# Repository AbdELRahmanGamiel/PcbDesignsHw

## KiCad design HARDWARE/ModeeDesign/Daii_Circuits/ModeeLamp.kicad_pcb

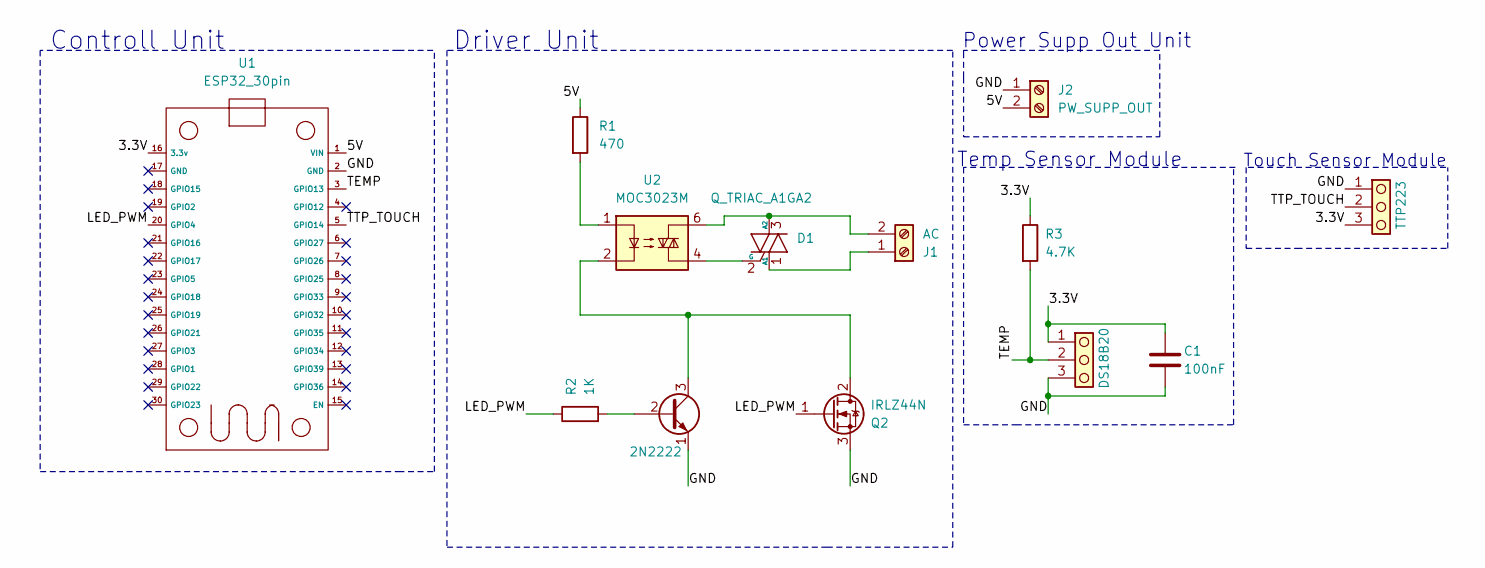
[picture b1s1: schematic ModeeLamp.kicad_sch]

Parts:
C1: 100nF; C_Disc_D5.0mm_W2.5mm_P2.50mm
D1: Q_TRIAC_A1GA2; TO-220-3_Vertical
J1: AC; Altech_AK100_1x02_P5.00mm
J2: PW_SUPP_OUT; Altech_AK100_1x02_P5.00mm
J3: DS18B20; Altech_AK100_1x03_P5.00mm
J4: TTP223; Altech_AK100_1x03_P5.00mm
Q1: 2N2222; TO-92L
Q2: IRLZ44N; TO-220-3_Vertical
R1: 470; R_Axial_DIN0204_L3.6mm_D1.6mm_P7.62mm_Horizontal
R2: 1K; R_Axial_DIN0204_L3.6mm_D1.6mm_P7.62mm_Horizontal
R3: 4.7K; R_Axial_DIN0204_L3.6mm_D1.6mm_P7.62mm_Horizontal
U1: ESP32_30pin
U2: MOC3023M; DIP-6_W7.62mm

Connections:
/3.3V: C1.1, J3.1, J4.3, R3.1, U1.16 (3.3v)
/5V: J2.2, R1.1, U1.1 (VIN)
/GND: C1.2, J2.1, J3.3, J4.1, Q1.1 (E), Q2.3 (S), U1.2 (GND)
/LED_PWM: Q2.1 (G), R2.1, U1.20 (GPIO4)
/TEMP: J3.2, R3.2, U1.3 (GPIO13)
/TTP_TOUCH: J4.2, U1.5 (GPIO14)
unnamed: D1.1 (A1), J1.1
unnamed: D1.3 (A2), J1.2, U2.6
unnamed: D1.2 (G), U2.4
unnamed: Q1.2 (B), R2.2
unnamed: Q1.3 (C), Q2.2 (D), U2.2
unnamed: R1.2, U2.1

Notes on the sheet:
Controll Unit
Temp Sensor Module
Power Supp Out Unit
Touch Sensor Module
Driver Unit

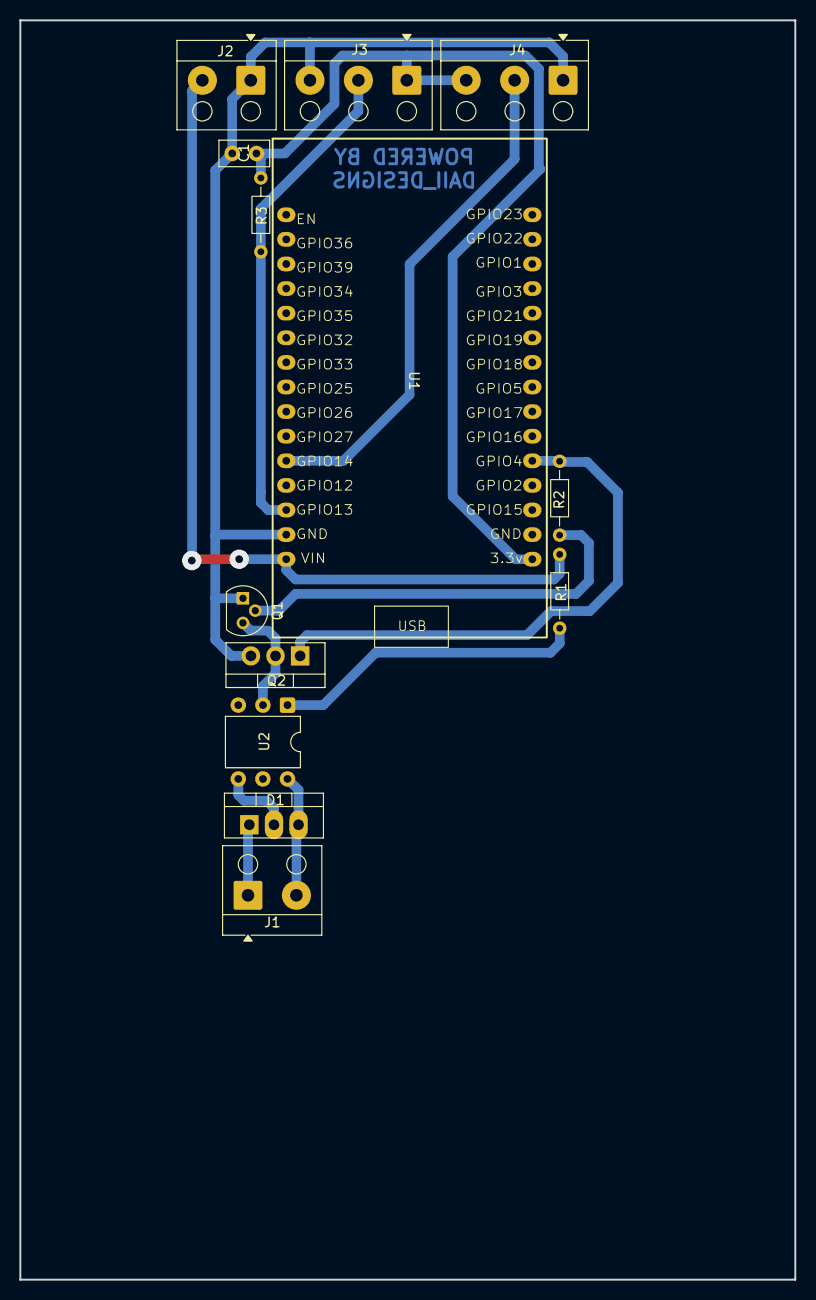
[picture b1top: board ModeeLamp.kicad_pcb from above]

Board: 2 copper layers, 80.0 x 130.0 mm, 13 parts (0 on the bottom side), 12 nets.

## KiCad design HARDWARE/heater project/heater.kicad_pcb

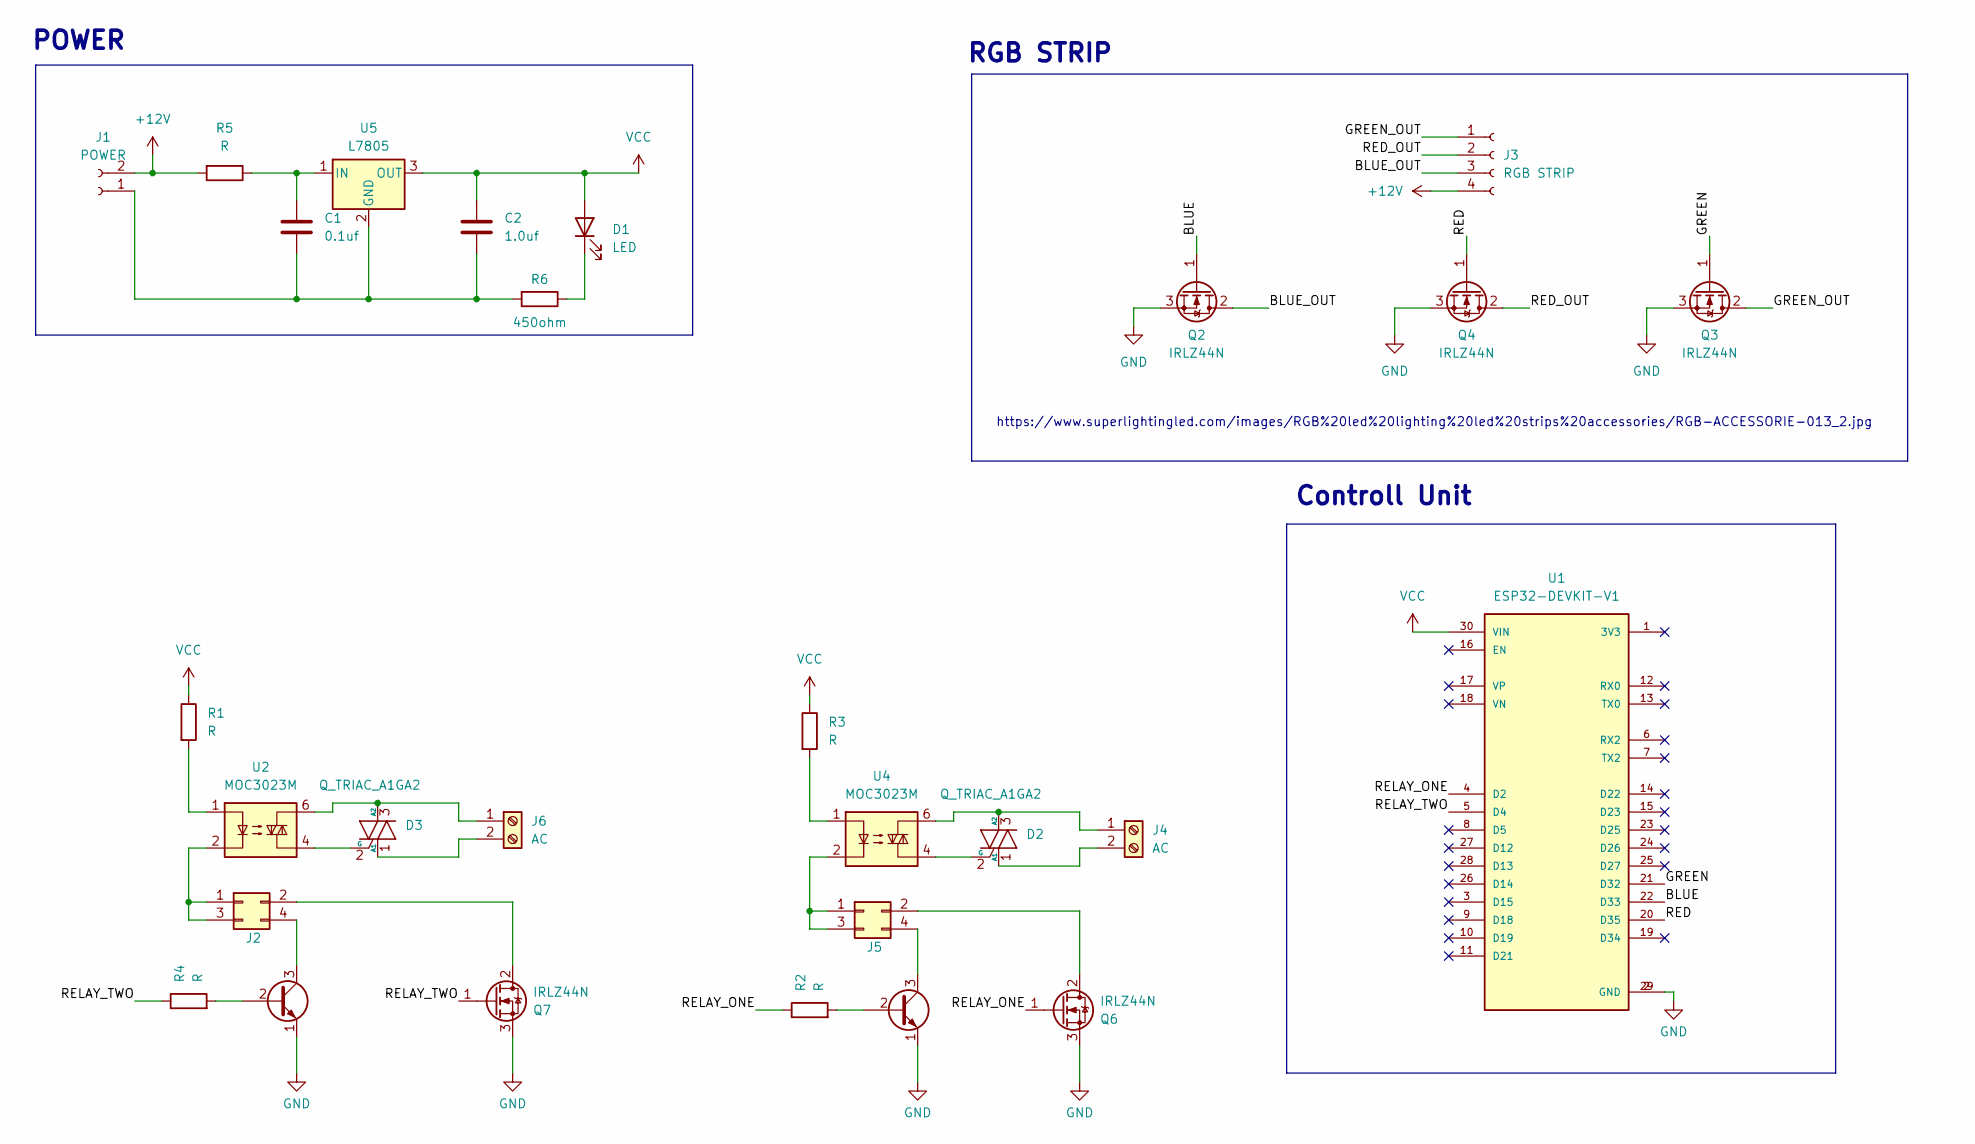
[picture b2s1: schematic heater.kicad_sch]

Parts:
C1: 0.1uf; CP_Radial_D8.0mm_P2.50mm
C2: 1.0uf; CP_Radial_D8.0mm_P2.50mm
D1: LED; LED_D3.0mm
D2, D3: Q_TRIAC_A1GA2; TO-220-3_Vertical
J1: POWER; TerminalBlock_Altech_AK300-2_P5.00mm
J2, J5: Conn_02x02_Odd_Even; PinHeader_2x02_P2.54mm_Vertical
J3: RGB STRIP; PinHeader_1x04_P2.54mm_Vertical
J4, J6: AC; TerminalBlock_Altech_AK300-2_P5.00mm
Q1, Q5: 2N2222; TO-92L
Q2, Q3, Q4, Q6, Q7: IRLZ44N; TO-220-3_Vertical
R1, R2, R3, R4: R; R_Axial_DIN0204_L3.6mm_D1.6mm_P7.62mm_Horizontal
R5: R; R_Axial_DIN0516_L15.5mm_D5.0mm_P25.40mm_Horizontal
R6: 450ohm; R_Axial_DIN0204_L3.6mm_D1.6mm_P7.62mm_Horizontal
U1: ESP32-DEVKIT-V1; MODULE_ESP32_DEVKIT_V1; PARTREV N/A
U2, U4: MOC3023M; DIP-6_W7.62mm
U5: L7805; TO-220-3_Vertical

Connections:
+12V: J1.2, J3.4, R5.2
/BLUE: Q2.1 (G), U1.22 (D33)
/BLUE_OUT: J3.3, Q2.2 (D)
/GREEN: Q3.1 (G), U1.21 (D32)
/GREEN_OUT: J3.1, Q3.2 (D)
/RED: Q4.1 (G), U1.20 (D35)
/RED_OUT: J3.2, Q4.2 (D)
/RELAY_ONE: Q6.1 (G), R2.1, U1.4 (D2)
/RELAY_TWO: Q7.1 (G), R4.1, U1.5 (D4)
GND: Q1.1 (E), Q2.3 (S), Q3.3 (S), Q4.3 (S), Q5.1 (E), Q6.3 (S), Q7.3 (S), U1.2 (GND), U1.29 (GND)
unnamed: D1.1 (K), R6.1
unnamed: D2.1 (A1), J4.2
unnamed: D2.3 (A2), J4.1, U4.6
unnamed: D2.2 (G), U4.4
unnamed: D3.1 (A1), J6.2
unnamed: D3.3 (A2), J6.1, U2.6
unnamed: D3.2 (G), U2.4
unnamed: C1.2, C2.2, J1.1, R6.2, U5.2 (GND)
unnamed: J2.1, J2.3, U2.2
unnamed: J2.2, Q7.2 (D)
unnamed: J2.4, Q1.3 (C)
unnamed: J5.1, J5.3, U4.2
unnamed: J5.2, Q6.2 (D)
unnamed: J5.4, Q5.3 (C)
unnamed: Q1.2 (B), R4.2
unnamed: Q5.2 (B), R2.2
unnamed: R1.2, U2.1
unnamed: R3.2, U4.1
unnamed: C1.1, R5.1, U5.1 (IN)
VCC: C2.1, D1.2 (A), R1.1, R3.1, U1.30 (VIN), U5.3 (OUT)

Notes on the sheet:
POWER
https://www.superlightingled.com/images/RGB%20led%20lighting%20led%20strips%20accessories/RGB-ACCESSORIE-013_2.jpg
Controll Unit
RGB STRIP

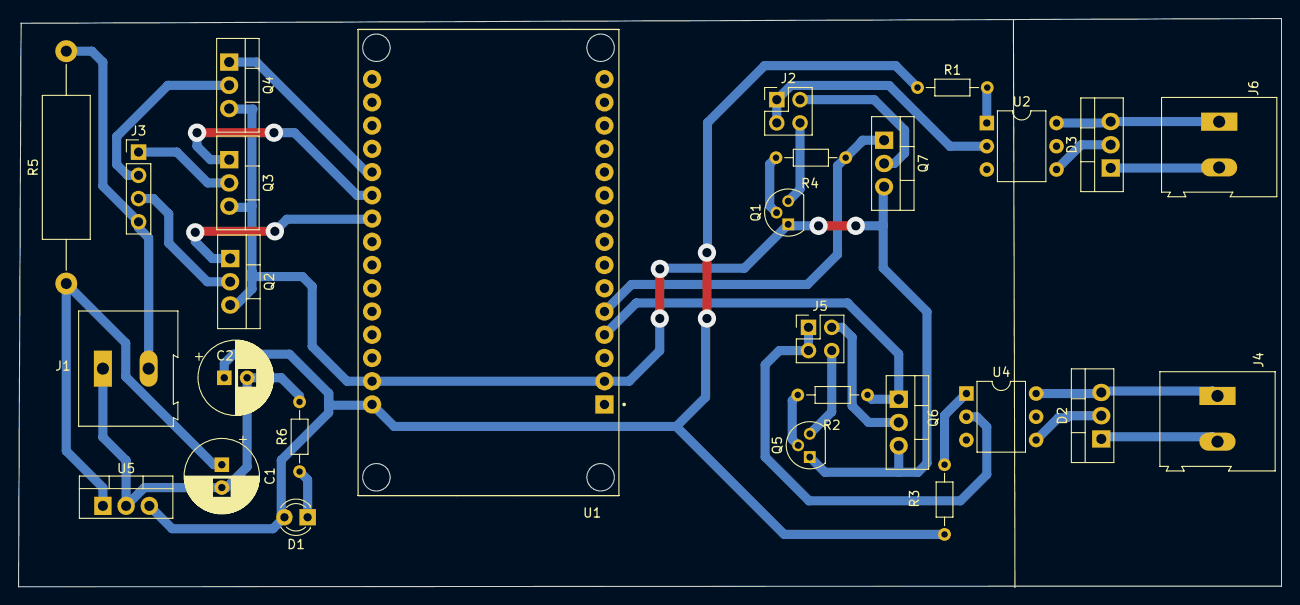
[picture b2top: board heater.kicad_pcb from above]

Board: 2 copper layers, 138.1 x 62.1 mm, 28 parts (0 on the bottom side), 30 nets.

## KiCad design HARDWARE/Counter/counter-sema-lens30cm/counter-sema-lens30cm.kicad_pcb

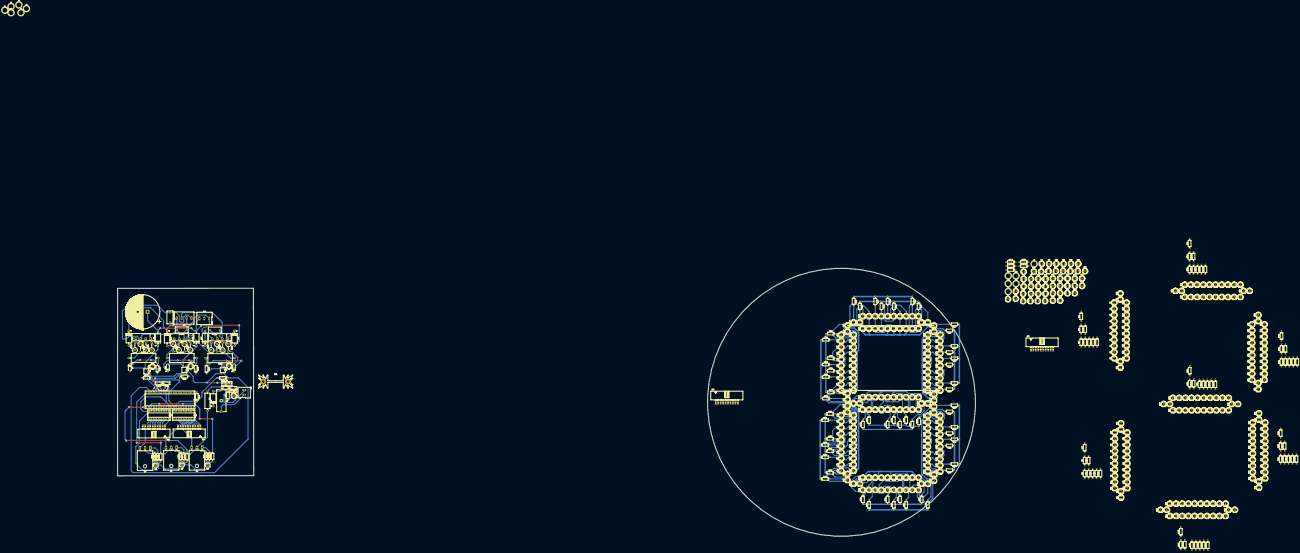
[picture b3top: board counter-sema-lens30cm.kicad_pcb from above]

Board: 2 copper layers, 597 parts (0 on the bottom side), 91 nets.

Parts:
AC_C1, AC_C2, AC_C3: 104\400V; C_Rect_L13.0mm_W6.0mm_P10.00mm_FKS3_FKP3_MKS4
C1: .33UF/25V; C_Disc_D7.0mm_W2.5mm_P5.00mm
C2: .1UF/25V; C_Disc_D7.0mm_W2.5mm_P5.00mm
C3: C-Device; CP_Radial_D35.0mm_P10.00mm_SnapIn
D1, D3, D7, D8, D12, D13, D17: 5408/3A; D_DO-27_P15.24mm_Horizontal
D2: LED_RED; LED_D5.0mm
D4: LED_R; LED_D5.0mm
D5, D10, D15: KBU808; Diode_Bridge_Vishay_KBU
D6, D11, D16: D_Zener_16v; D_A-405_P7.62mm_Horizontal
D9: LED_G; LED_D5.0mm
D14: LED_Y; LED_D5.0mm
F1: 1A; Fuseholder_Cylinder-5x20mm_Schurter_0031_8201_Horizontal_Op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
G1, G2, G3, G4, G5, G6, G7, G8, G9, G10, G11, G12, G13, G14, G15, G16, G17, G18, G19, G20, G21, G22, G23, G24, G25, G26, G27, G28, G29, G30, G31, G32, G33, G34, G35, G36, G37, G38, G39, G40, G41, G42, G43, G44, G45, G46, G47, G48, G49, G50, G51, G52, G53, G54, G55, G56, G57, G58, G59, G60, G61, G62, G63, G64, G65, G66, G67, G68, G69, G70, G71, G72, G73, G74, G75, G76, G77, G78, G79, G80, G81, G82, G83, G84, G85, G86, G87, G88, G89, G90, G91, G92, G93, G94, G95, G96, G97, G98, G99, G100, G101, G102, G103, G104, G105, G106, G107, G108, G109, G110, G111, G112, G113, G114, G115, G116, G117, G118, G119, G120, G121, G122, G123, G124, G125, G126, G127, G128, G129, G130, G131, G132, G133, G134, G135, G136, G137, G138, G139, G140, G141, G142, G143, G144, G145, G146, G147, G148, G149, G150, G151, G152, G153, G154, G155, G156, G157, G158, G159, G160, G161, G162, G163, G164, G165, G166, G167, G168: LED; LED_D5.0mm_centerd_modified-pad
HS1: Heatsink; Heatsink_Fischer_SK104-STC-STIC_35x13mm_2xDrill2.5mm
J1, J2, J3, J4, J5, J6, J7, J8, J9, J10, J11, J12: Screw_Terminal_01x01; TestPoint_Plated_Hole_D5.0mm
J13: COLOR_220_I/P; TerminalBlock_Altech_AK300-4_P5.00mm
J14: DC220V_O/P; TerminalBlock_Altech_AK300-3_P5.00mm
J15: DC12V_I/P; TerminalBlock_Altech_AK300-2_P5.00mm
J16: TENS_SOCKET_SEG; Multicomp_MC9A22-2034_2x10_P2.54mm_Horizontal
J17: UNITS_SOCKET; Multicomp_MC9A22-2034_2x10_P2.54mm_Horizontal
J18: TENS_SOCKET; Multicomp_MC9A22-2034_2x10_P2.54mm_Horizontal
J19: UNITS_SOCKET_SEG; Multicomp_MC9A22-2034_2x10_P2.54mm_Horizontal
PIC_C1: 104\25V; C_Disc_D7.0mm_W2.5mm_P5.00mm
PIC_C2, PIC_C3: 22p\25V; C_Disc_D7.0mm_W2.5mm_P5.00mm
Q1, Q2, Q3: 2N2222; TO-92L_HandSolder
Q4, Q5, Q6: TIP147; TO-3P-3_Horizontal_TabDown
R1: 10R-500mA-3WATT/20R-250mA2-WATT; R_Axial_DIN0516_L15.5mm_D5.0mm_P20.32mm_Horizontal
R2: 220R; R_Axial_DIN0207_L6.3mm_D2.5mm_P10.16mm_Horizontal
R3, R4, R5, R6, R7, R8, R9, R10, R11, R12, R13, R14, R15, R16, R17, R18, R19, R20, R21, R22, R23, R24, R25, R26, R27, R28, R29, R30, R31, R32, R33, R34, R35, R36, R37, R38, R39, R40, R41, R42, R43, R44, R45, R46, R47, R48, R49, R50, R51, R52, R53, R54, R55, R56, R57, R58, R59, R60, R61, R62, R63, R64, R65, R66, R67, R68, R69, R70, R71, R72, R73, R74, R75, R76, R77, R78, R79, R80, R81, R82, R83, R84, R85, R86, R87, R88, R89, R90, R91, R92, R93, R94, R95, R96, R97, R98, R99, R100, R101, R102, R103, R104, R105, R106, R107, R108, R109, R110, R111, R112, R113, R114, R115, R116, R117, R118, R119, R120, R121, R122, R123, R124, R125, R126, R127, R128, R129, R130, R131, R132, R133, R134, R135, R136, R137, R138, R139, R140, R141, R142, R143, R144, R145, R146, R147, R148, R149, R150, R151, R152, R153, R154, R155, R156, R157, R158, R159, R160, R161, R162, R163, R164, R165, R166, R167, R168, R169, R170: LED; LED_D5.0mm_centerd_modified-pad
R171, R172, R173, R174, R175: 820R/.5W; R_Axial_DIN0207_L6.3mm_D2.5mm_P10.16mm_Horizontal
R176, R183, R190: 1k; R_Axial_DIN0207_L6.3mm_D2.5mm_P10.16mm_Horizontal
R177, R184, R191, R197, R201, R202, R203: 10K; R_Axial_DIN0207_L6.3mm_D2.5mm_P10.16mm_Horizontal
R178, R185, R192: 22k/3w-20k/1w; R_Axial_Power_L25.0mm_W9.0mm_P30.48mm
R179, R180, R181, R182, R186, R187, R188, R189, R193, R194, R195, R196: 2.2k/2w; R_Axial_DIN0516_L15.5mm_D5.0mm_P7.62mm_Vertical
R198, R199, R200: 1K; R_Axial_DIN0207_L6.3mm_D2.5mm_P10.16mm_Horizontal
R204, R205, R206: 332R; R_Axial_DIN0207_L6.3mm_D2.5mm_P10.16mm_Horizontal
Rg1, Rg2, Rg3, Rg4, Rg5, Rg6, Rg7, Rg8, Rg9, Rg10, Rg11, Rg12, Rg13, Rg14, Rg15, Rg16, Rg17, Rg18, Rg19, Rg20, Rg21, Rg22, Rg23, Rg24, Rg25, Rg26, Rg27, Rg28, Rg29, Rg30, Rg31, Rg32, Rg33, Rg34, Rg35, Rg36, Rg37, Rg38, Rg39, Rg40, Rg41, Rg42, Rg43, Rg44, Rg45, Rg46, Rg47, Rg48, Rg49, Rg50, Rg51, Rg52, Rg53, Rg54, Rg55, Rg56: 160R; R_Axial_DIN0207_L6.3mm_D2.5mm_P10.16mm_Horizontal
Rr1, Rr2, Rr3, Rr4, Rr5, Rr6, Rr7, Rr8, Rr9, Rr10, Rr11, Rr12, Rr13, Rr14, Rr15, Rr16, Rr17, Rr18, Rr19, Rr20, Rr21, Rr22, Rr23, Rr24, Rr25, Rr26, Rr27, Rr28, Rr29, Rr30, Rr31, Rr32, Rr33, Rr34, Rr35, Rr36, Rr37, Rr38, Rr39, Rr40, Rr41, Rr42, Rr43, Rr44, Rr45, Rr46, Rr47, Rr48, Rr49, Rr50, Rr51, Rr52, Rr53, Rr54, Rr55, Rr56: 380R; R_Axial_DIN0207_L6.3mm_D2.5mm_P10.16mm_Horizontal
U1: LM7805_TO220; TO-220-3_Vertical
U2, U3, U4: PC817; DIP-4_W7.62mm
U5: PIC16F877A-IP; DIP-40_W15.24mm_Socket_LongPads
U6, U7: ULN2803A; DIP-18_W7.62mm_Socket_LongPads
Y1, Y2, Y3, Y4, Y5, Y6, Y7, Y8, Y9, Y10, Y11, Y12, Y13, Y14, Y15, Y16, Y17, Y18, Y19, Y20, Y21, Y22, Y23, Y24, Y25, Y26, Y27, Y28, Y29, Y30, Y31, Y32, Y33, Y34, Y35, Y36, Y37, Y38, Y39, Y40, Y41, Y42, Y43, Y44, Y45, Y46, Y47, Y48, Y49, Y50: LED; LED_D5.0mm_centerd_modified-pad
Y51: Crystal_Small; Resonator-2Pin_W10.0mm_H5.0mm

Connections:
/COM_G_MCU: J17.19, J17.20, Q5.3
/COM_R_MCU: J17.17, J17.18, Q4.3
/COM_SIGNAL_G: R199.2, U5.21
/COM_SIGNAL_R: R198.2, U5.22
/COM_SIGNAL_Y: R200.2, U5.20
/COM_Y_MCU: J18.17, J18.18, Q6.3
/DC220_+: C3.2, D7.1, D12.1, D17.1, J14.3
/DC220_-: C3.1, D3.2, D8.2, D13.2, J14.1
/GND: C1.2, C2.2, J15.1, PIC_C1.2, PIC_C2.1, PIC_C3.1, Q1.1, Q2.1, Q3.1, R2.2, U1.2, U2.3, U3.3, U4.3, U5.12, U5.31, U6.9, U7.9
/I-P_signal_G: R184.1, U3.4, U5.18
/I-P_signal_R: R177.1, U2.4, U5.17
/I-P_signal_Y: R191.1, U4.4, U5.19
/L_G: AC_C2.1, D10.2, J13.2
/L_R: AC_C1.1, D5.2, J13.1
/L_Y: AC_C3.1, D15.2, J13.3
/N: AC_C1.2, AC_C2.2, AC_C3.2, D5.3, D10.3, D15.3, J13.4
/VCC_5V: C2.1, D2.2, PIC_C1.1, R177.2, R184.2, R191.2, R197.2, U1.3, U5.11, U5.32
/VDD_12V: D1.1, Q4.2, Q5.2, Q6.2, R1.2, R201.2, R202.2, R203.2
/V_INPUT_12VDC: F1.2, J15.2
/YELLOW: U5.23, U7.8
/a-tens: U5.30, U7.1
/a-units: U5.40, U6.1
/b-tens: U5.29, U7.2
/b-units: U5.39, U6.2
/c-tens: U5.28, U7.3
/c-units: U5.38, U6.3
/d-tens: U5.27, U7.4
/d-units: U5.37, U6.4
/e-tens: U5.26, U7.5
/e-units: U5.36, U6.5
/f-tens: U5.25, U7.6
/f-units: U5.35, U6.6
/g-tens: U5.24, U7.7
/g-units: U5.34, U6.7
/spare-units: U5.33, U6.8
unnamed: C1.1, R1.1, U1.1
unnamed: D1.2, F1.1
unnamed: D2.1, R2.1
unnamed: D3.1, D5.1, D6.2, R182.2, U2.2
unnamed: D4.1, U2.1
unnamed: D4.2, R176.2
unnamed: D5.4, D7.2, R179.1
unnamed: D6.1, R176.1, R178.2
unnamed: D9.1, U3.1
unnamed: D9.2, R183.2
unnamed: D8.1, D10.1, D11.2, R189.2, U3.2
unnamed: D10.4, D12.2, R186.1
unnamed: D11.1, R183.1, R185.2
unnamed: D13.1, D15.1, D16.2, R196.2, U4.2
unnamed: D14.1, U4.1
unnamed: D14.2, R190.2
unnamed: D15.4, D17.2, R193.1
unnamed: D16.1, R190.1, R192.2
unnamed: J17.1, J17.2, U6.18
unnamed: J17.3, J17.4, U6.17
unnamed: J17.5, J17.6, U6.16
unnamed: J17.7, J17.8, U6.15
unnamed: J17.9, J17.10, U6.14
unnamed: J17.11, J17.12, U6.13
unnamed: J17.13, J17.14, U6.12
unnamed: J17.15, J17.16, U6.11
unnamed: J18.1, J18.2, U7.18
unnamed: J18.3, J18.4, U7.17
unnamed: J18.5, J18.6, U7.16
unnamed: J18.7, J18.8, U7.15
unnamed: J18.9, J18.10, U7.14
unnamed: J18.11, J18.12, U7.13
unnamed: J18.13, J18.14, U7.12
unnamed: J18.15, J18.16, U7.11
unnamed: J18.19, J18.20
unnamed: PIC_C2.2, U5.13, Y51.2
unnamed: PIC_C3.2, U5.14, Y51.1
unnamed: Q1.2, R198.1
unnamed: Q1.3, R201.1, R204.1
unnamed: Q2.2, R199.1
unnamed: Q2.3, R202.1, R205.1
unnamed: Q3.2, R200.1
unnamed: Q3.3, R203.1, R206.1
unnamed: Q4.1, R204.2
unnamed: Q5.1, R205.2
unnamed: Q6.1, R206.2
unnamed: R178.1, R180.2, R181.1
unnamed: R179.2, R180.1
unnamed: R181.2, R182.1
unnamed: R185.1, R187.2, R188.1
unnamed: R186.2, R187.1
unnamed: R188.2, R189.1
unnamed: R192.1, R194.2, R195.1
unnamed: R193.2, R194.1
unnamed: R195.2, R196.1
unnamed: R197.1, U5.1

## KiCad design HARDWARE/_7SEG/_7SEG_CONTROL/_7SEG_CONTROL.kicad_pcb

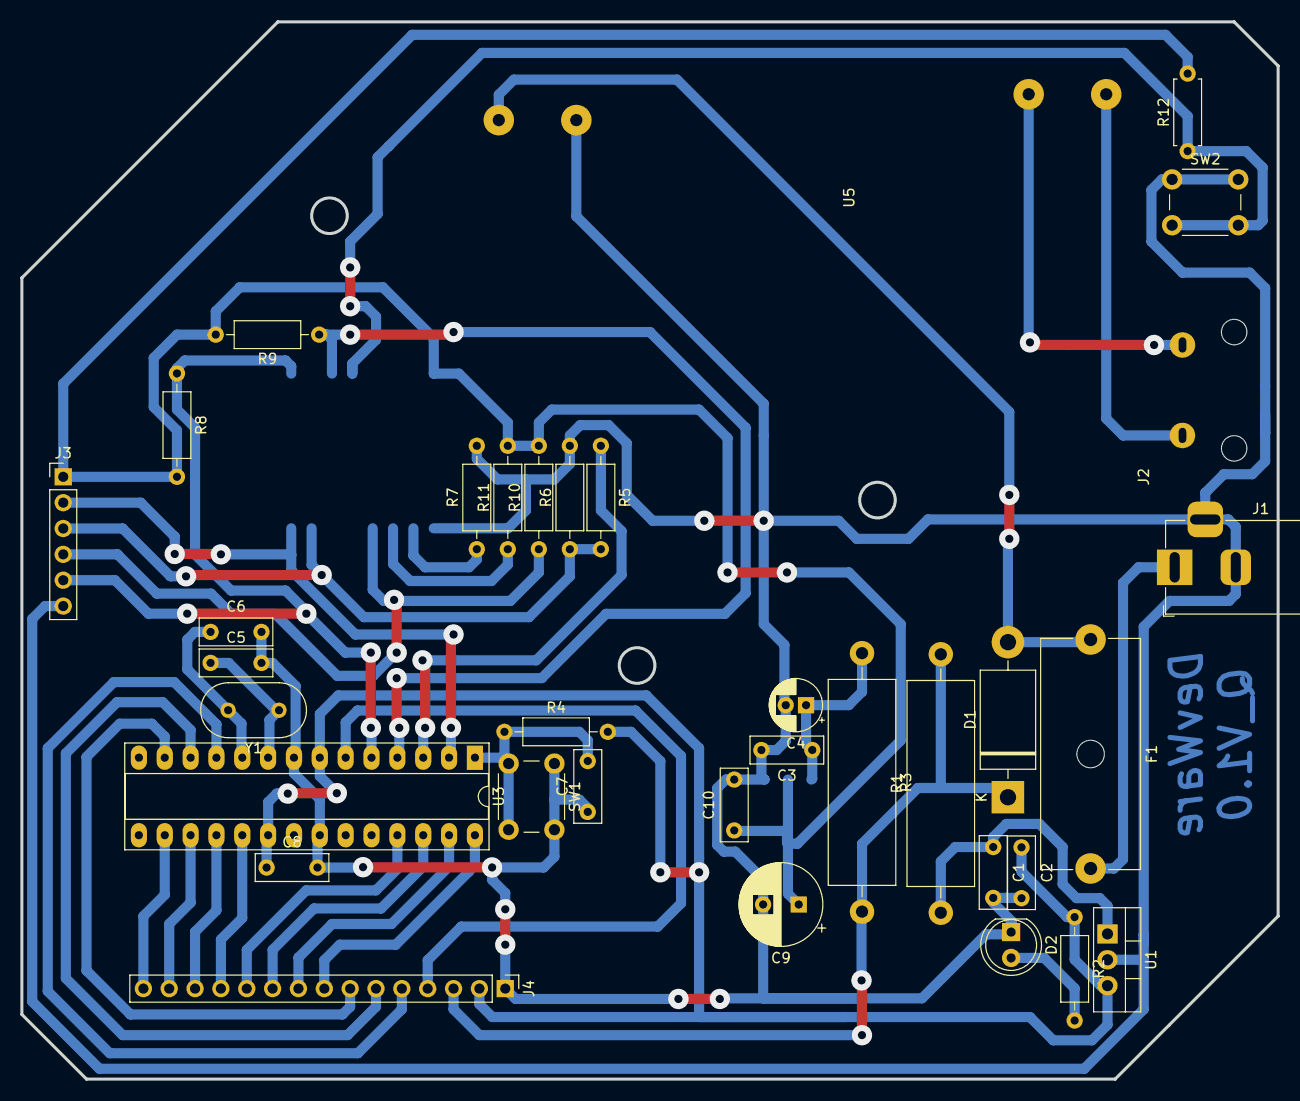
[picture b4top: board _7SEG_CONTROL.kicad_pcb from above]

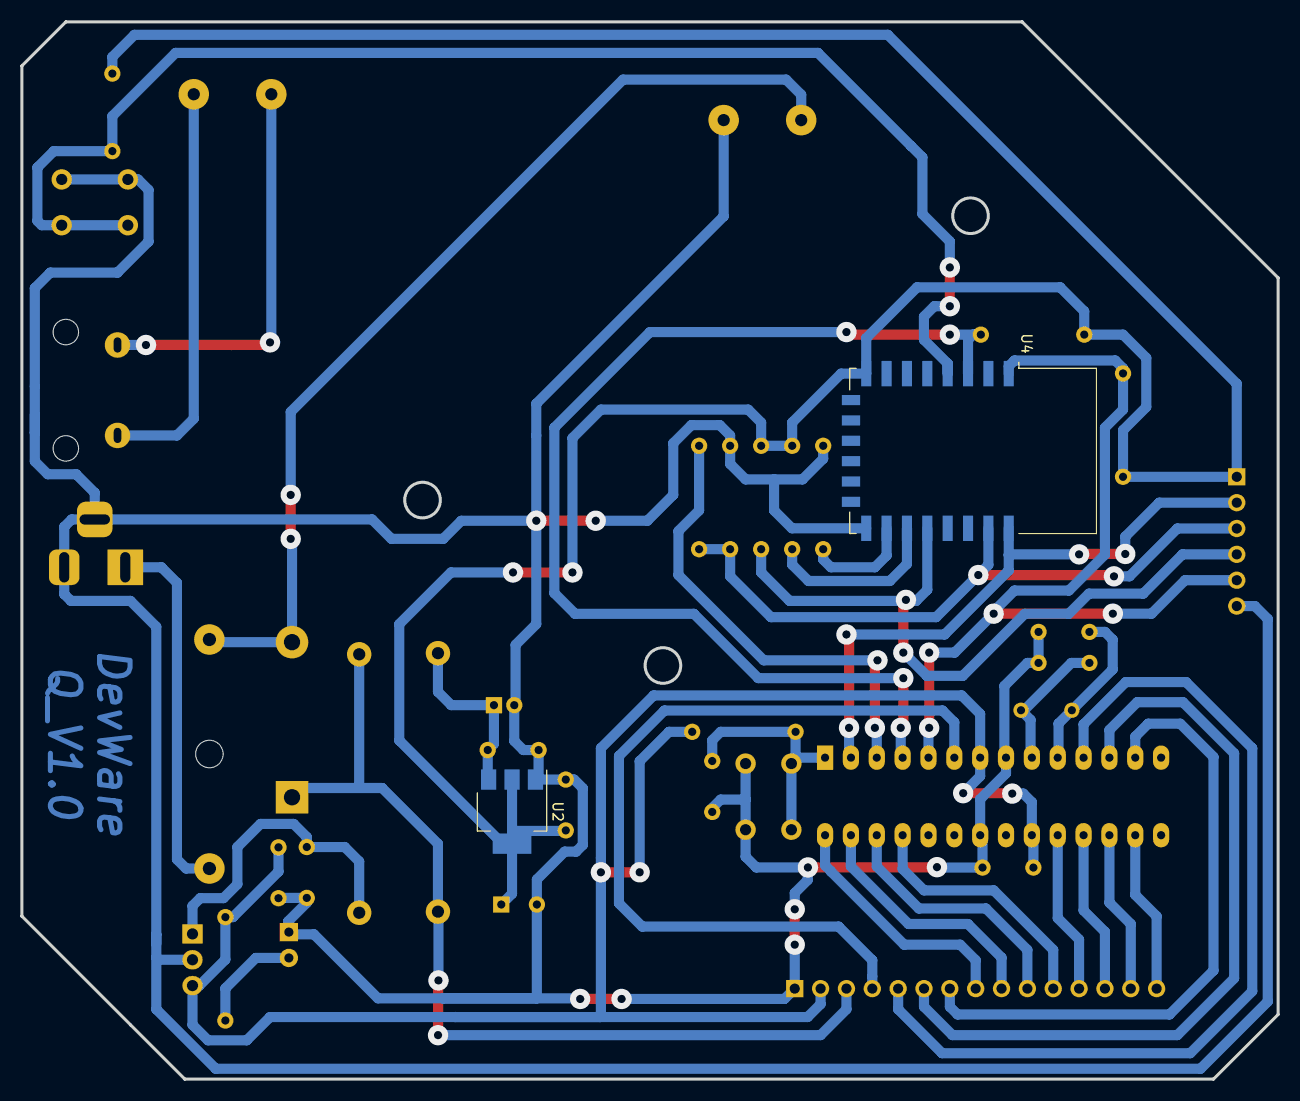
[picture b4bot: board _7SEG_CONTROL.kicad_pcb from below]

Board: 2 copper layers, 123.4 x 103.9 mm, 37 parts (2 on the bottom side), 35 nets.

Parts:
C1, C3: 334; C_Disc_D7.0mm_W2.5mm_P5.00mm
C2, C7, C10: 104; C_Disc_D7.0mm_W2.5mm_P5.00mm
C4: 10UF; CP_Radial_D5.0mm_P2.00mm
C5, C6: 22P; C_Disc_D7.0mm_W2.5mm_P5.00mm
C8: 0.1UF; C_Disc_D7.0mm_W2.5mm_P5.00mm
C9: 100UF; CP_Radial_D8.0mm_P3.50mm
D1: 1N5407; D_DO-201AD_P15.24mm_Horizontal
D2: LED; LED_D5.0mm
F1: Fuse; Fuseholder_Cylinder-5x20mm_Schurter_0031_8201_Horizontal_Op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
J1: Barrel_Jack_Switch; BarrelJack_Horizontal
J2: AC_Socket
J3: CONFIG_ESP12; PinHeader_1x06_P2.54mm_Vertical
J4: Display_Board; PinHeader_1x15_P2.54mm_Vertical
R1: 10/2W; R_Axial_Power_L20.0mm_W6.4mm_P25.40mm
R2: 330; R_Axial_DIN0207_L6.3mm_D2.5mm_P10.16mm_Horizontal
R3: 10/3W; R_Axial_Power_L20.0mm_W6.4mm_P25.40mm
R4, R5, R6: 10K; R_Axial_DIN0207_L6.3mm_D2.5mm_P10.16mm_Horizontal
R7, R8, R9, R10, R11: 12K; R_Axial_DIN0207_L6.3mm_D2.5mm_P10.16mm_Horizontal
R12: 10K; R_Axial_DIN0207_L6.3mm_D2.5mm_P7.62mm_Horizontal
SW1, SW2: SW_Push; SW_PUSH_6mm_H7.3mm
U1: L7805; TO-220-3_Vertical
U2: AMS1117-3.3; SOT-223-3_TabPin2
U3: ATmega328-PU; DIP-28_W7.62mm_Socket_LongPads
U4: ESP-12E
U5: PS-12VDC; PS_12VDC
Y1: 16MH; Resonator-2Pin_W10.0mm_H5.0mm

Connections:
/3.3V: C9.1, C10.1, J3.1, R8.2, R9.2, R10.2, R11.2, R12.2, U2.2, U4.8
/5V: C2.1, C8.1, J4.2, R2.1, R4.2, U1.3, U3.7, U3.20
/12V: D1.1, J4.3, R1.2, R3.2
/A_D1: J4.15, U3.16
/A_D2: J4.11, U3.25
/A_D3: J4.7, U3.13
/B_D1: J4.12, U3.19
/B_D2: J4.8, U3.28
/B_D3: J4.4, U3.6
/C_D1: J4.13, U3.18
/C_D2: J4.9, U3.27
/C_D3: J4.5, U3.11
/D_D1: J4.14, U3.17
/D_D2: J4.10, U3.26
/D_D3: J4.6, U3.12
/EN: R9.1, U3.4, U4.3
/GND: C1.2, C2.2, C3.2, C4.2, C5.2, C6.2, C7.1, C8.2, C9.2, C10.2, D2.1, J1.2, J1.3, J3.6, J4.1, R6.2, R7.2, SW1.1, SW2.1, U1.2, U2.1, U3.8, U3.22, U4.15, U5.3
/IO0: J3.4, R10.1, U4.18
/IO2: R11.1, U4.17
/IO15: R7.1, U4.16
/Interrupt: R12.1, SW2.2, U4.4
/RST: J3.5, R8.1, U3.5, U4.1
/RX-MCU: J3.2, U3.2, U4.22
/RXD: J3.3, R5.2, R6.1, U4.21
/TX_MCU: R5.1, U3.3
/V+: D1.2, F1.1, U5.4
unnamed: C1.1, R1.1, U1.1
unnamed: C3.1, C4.1, R3.1, U2.3
unnamed: C5.1, U3.9, Y1.1
unnamed: C6.1, U3.10, Y1.2
unnamed: C7.2, R4.1, SW1.2, U3.1
unnamed: D2.2, R2.2
unnamed: F1.2, J1.1
unnamed: J2.L, U5.1
unnamed: J2.N, U5.2

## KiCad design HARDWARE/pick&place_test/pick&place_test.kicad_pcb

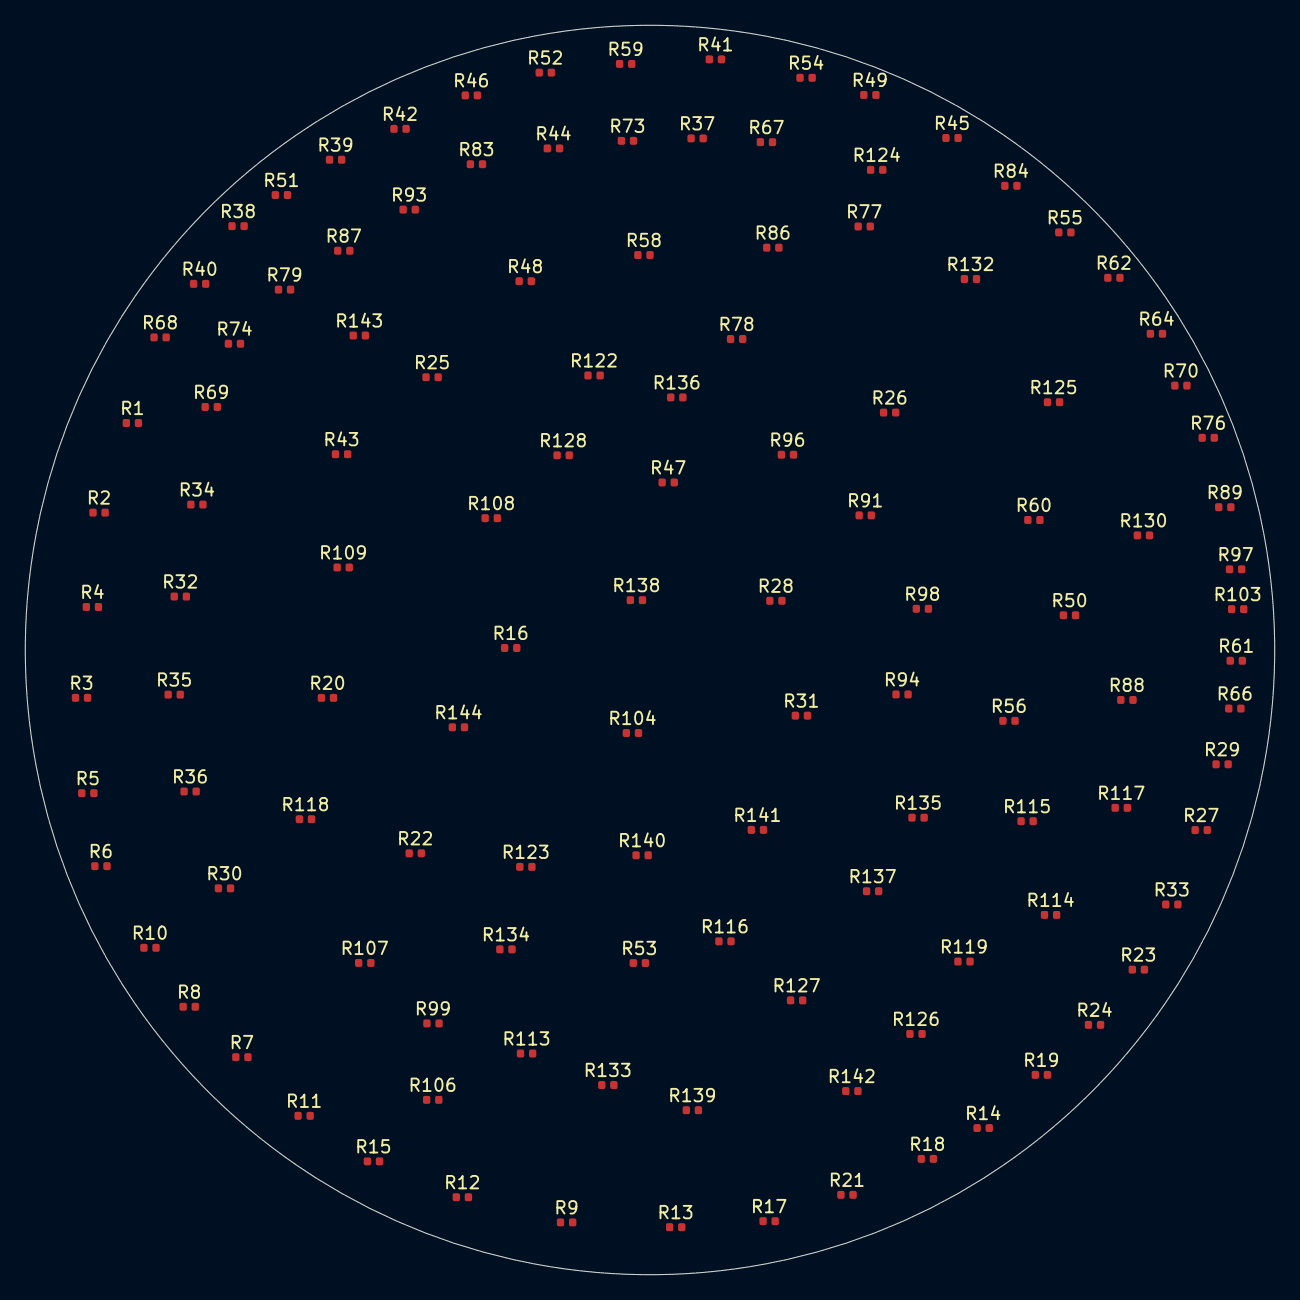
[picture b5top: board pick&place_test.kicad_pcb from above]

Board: 2 copper layers, 100.0 x 100.0 mm, 120 parts (0 on the bottom side), 101 nets, no tracks yet.

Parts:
R1, R2, R3, R4, R5, R6, R7, R8, R9, R10, R11, R12, R13, R14, R15, R16, R17, R18, R19, R20, R21, R22, R23, R24, R25, R26, R27, R28, R29, R30, R31, R32, R33, R34, R35, R36, R37, R38, R39, R40, R41, R42, R43, R44, R45, R46, R47, R48, R49, R50, R51, R52, R53, R54, R55, R56, R58, R59, R60, R61, R62, R64, R66, R67, R68, R69, R70, R73, R74, R76, R77, R78, R79, R83, R84, R86, R87, R88, R89, R91, R93, R94, R96, R97, R98, R99, R103, R104, R106, R107, R108, R109, R113, R114, R115, R116, R117, R118, R119, R122, R123, R124, R125, R126, R127, R128, R130, R132, R133, R134, R135, R136, R137, R138, R139, R140, R141, R142, R143, R144: R; R_0402_1005Metric

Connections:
unnamed: R1.1, R3.2
unnamed: R1.2, R2.1
unnamed: R2.2, R4.1
unnamed: R3.1, R5.2
unnamed: R4.2, R6.1
unnamed: R5.1, R7.2
unnamed: R6.2, R8.1
unnamed: R7.1, R9.2
unnamed: R8.2, R10.1
unnamed: R10.2, R12.1
unnamed: R11.1, R13.2
unnamed: R9.1, R11.2
unnamed: R12.2, R14.1
unnamed: R13.1, R15.2
unnamed: R14.2, R16.1
unnamed: R15.1, R17.2
unnamed: R16.2, R18.1
unnamed: R17.1, R19.2
unnamed: R18.2, R20.1
unnamed: R19.1, R21.2
unnamed: R20.2, R22.1
unnamed: R21.1, R23.2
unnamed: R22.2, R24.1
unnamed: R23.1, R25.1
unnamed: R24.2, R36.2
unnamed: R25.2, R26.1
unnamed: R26.2, R27.1
unnamed: R27.2, R28.1
unnamed: R28.2, R29.1
unnamed: R29.2, R30.1
unnamed: R30.2, R31.1
unnamed: R31.2, R32.1
unnamed: R32.2, R33.1
unnamed: R33.2, R34.1
unnamed: R34.2, R35.1
unnamed: R35.2, R36.1
unnamed: R37.1, R39.2
unnamed: R37.2, R38.1
unnamed: R38.2, R40.1
unnamed: R39.1, R41.2
unnamed: R40.2, R42.1
unnamed: R41.1, R43.2
unnamed: R42.2, R44.1
unnamed: R43.1, R45.2
unnamed: R44.2, R46.1
unnamed: R45.1, R47.2
unnamed: R46.2, R48.1
unnamed: R47.1, R49.2
unnamed: R48.2, R50.1
unnamed: R49.1, R51.2
unnamed: R50.2, R52.1
unnamed: R51.1, R53.2
unnamed: R52.2, R54.1
unnamed: R53.1, R55.2
unnamed: R54.2, R56.1
unnamed: R56.2, R58.1
unnamed: R58.2, R60.1
unnamed: R59.1, R61.1
unnamed: R61.2, R62.1
unnamed: R66.2, R67.1
unnamed: R67.2, R68.1
unnamed: R68.2, R69.1
unnamed: R69.2, R70.1
unnamed: R73.2, R74.1
unnamed: R74.2, R76.1
unnamed: R77.2, R78.1
unnamed: R79.1, R83.2
unnamed: R83.1, R87.2
unnamed: R84.2, R88.1
unnamed: R87.1, R91.2
unnamed: R89.1, R93.2
unnamed: R93.1, R97.2
unnamed: R94.2, R98.1
unnamed: R103.1, R107.2
unnamed: R99.1, R103.2
unnamed: R104.2, R108.1
unnamed: R109.1, R113.2
unnamed: R114.2, R130.1
unnamed: R115.1, R117.1
unnamed: R116.2, R128.2
unnamed: R117.2, R118.1
unnamed: R118.2, R119.1
unnamed: R122.2, R123.1
unnamed: R123.2, R124.1
unnamed: R124.2, R125.1
unnamed: R125.2, R126.1
unnamed: R126.2, R127.1
unnamed: R127.2, R128.1
unnamed: R130.2, R132.1
unnamed: R132.2, R144.2
unnamed: R133.2, R134.1
unnamed: R134.2, R135.1
unnamed: R135.2, R136.1
unnamed: R136.2, R137.1
unnamed: R137.2, R138.1
unnamed: R138.2, R139.1
unnamed: R139.2, R140.1
unnamed: R140.2, R141.1
unnamed: R141.2, R142.1
unnamed: R142.2, R143.1
unnamed: R143.2, R144.1
